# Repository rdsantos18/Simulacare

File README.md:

# SimulaCare
<<<<<<< HEAD
SimulaCare RCP
Versao WIFI + BLUETOOTH
=======
SimulaCare RCP Versao WI-FI

>>>>>>> 4a381d82d7e9b7c94d12f0bdcbb5406eb2f44847

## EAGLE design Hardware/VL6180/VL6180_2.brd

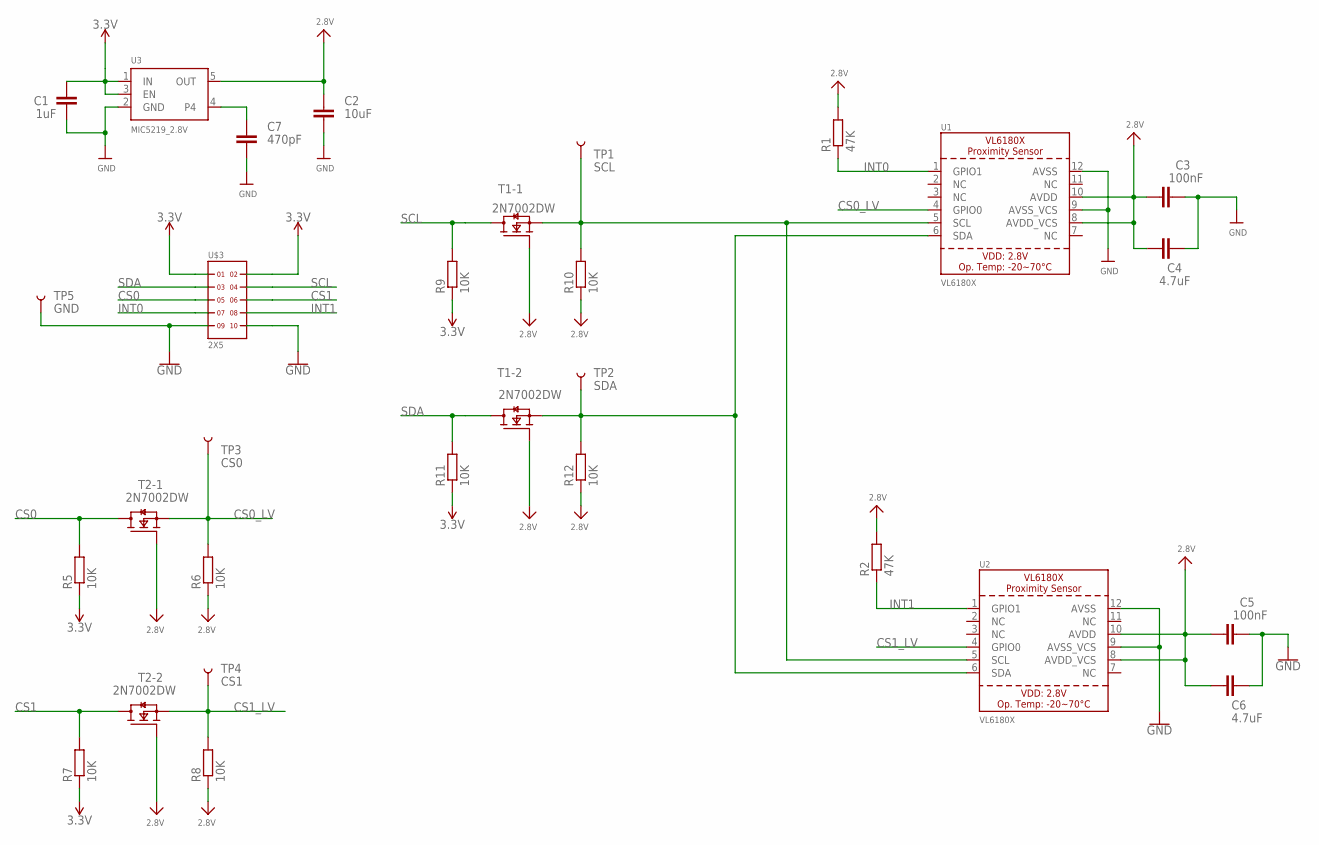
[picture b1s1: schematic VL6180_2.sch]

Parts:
C1: 1uF; C0603
C2: 10uF; C0603
C3, C5: 100nF; C0603
C4, C6: 4.7uF; C0603
C7: 470pF; C0603
R1, R2: 47K; R0603
R5, R6, R7, R8, R9, R10, R11, R12: 10K; R0603
T1, T2: 2N7002DW; SOT363
TP1: SCL; PAD.03X.04
TP2: SDA; PAD.03X.04
TP3: CS0; PAD.03X.04
TP4: CS1; PAD.03X.04
TP5: GND; PAD.03X.04
U1, U2: VL6180X; VL6180
U3: MIC5219_2.8V; SOT23-5
U$3: 2X5

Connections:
2.8V: C2.1, C3.1, C4.1, C5.1, C6.1, R1.2, R2.2, R6.1, R8.1, R10.1, R12.1, T1.2 (G), T1.5 (G), T2.2 (G), T2.5 (G), U1.8 (AVDD_VCS), U1.10 (AVDD), U2.8 (AVDD_VCS), U2.10 (AVDD), U3.5 (OUT)
3.3V: C1.1, R5.1, R7.1, R9.1, R11.1, U3.1 (IN), U3.3 (EN), U$3.1, U$3.2
CS0: R5.2, T2.6 (D), U$3.5
CS0_LV: R6.2, T2.1 (S), TP3.P$1, U1.4 (GPIO0)
CS1: R7.2, T2.3 (D), U$3.6
CS1_LV: R8.2, T2.4 (S), TP4.P$1, U2.4 (GPIO0)
GND: C1.2, C2.2, C3.2, C4.2, C5.2, C6.2, C7.2, TP5.P$1, U1.9 (AVSS_VCS), U1.12 (AVSS), U2.9 (AVSS_VCS), U2.12 (AVSS), U3.2 (GND), U$3.9, U$3.10
INT0: R1.1, U1.1 (GPIO1), U$3.7
INT1: R2.1, U2.1 (GPIO1), U$3.8
unnamed: C7.1, U3.4
unnamed: R10.2, T1.1 (S), TP1.P$1, U1.5 (SCL), U2.5 (SCL)
unnamed: R12.2, T1.4 (S), TP2.P$1, U1.6 (SDA), U2.6 (SDA)
SCL: R9.2, T1.6 (D), U$3.4
SDA: R11.2, T1.3 (D), U$3.3

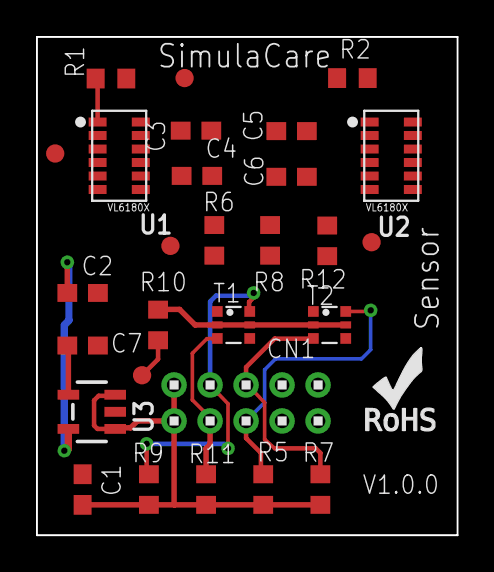
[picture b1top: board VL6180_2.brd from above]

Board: 2 copper layers, 23.4 x 27.7 mm, 29 parts (0 on the bottom side), 14 nets.

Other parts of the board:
U$20: ROHS_LOGO_0.18_IN

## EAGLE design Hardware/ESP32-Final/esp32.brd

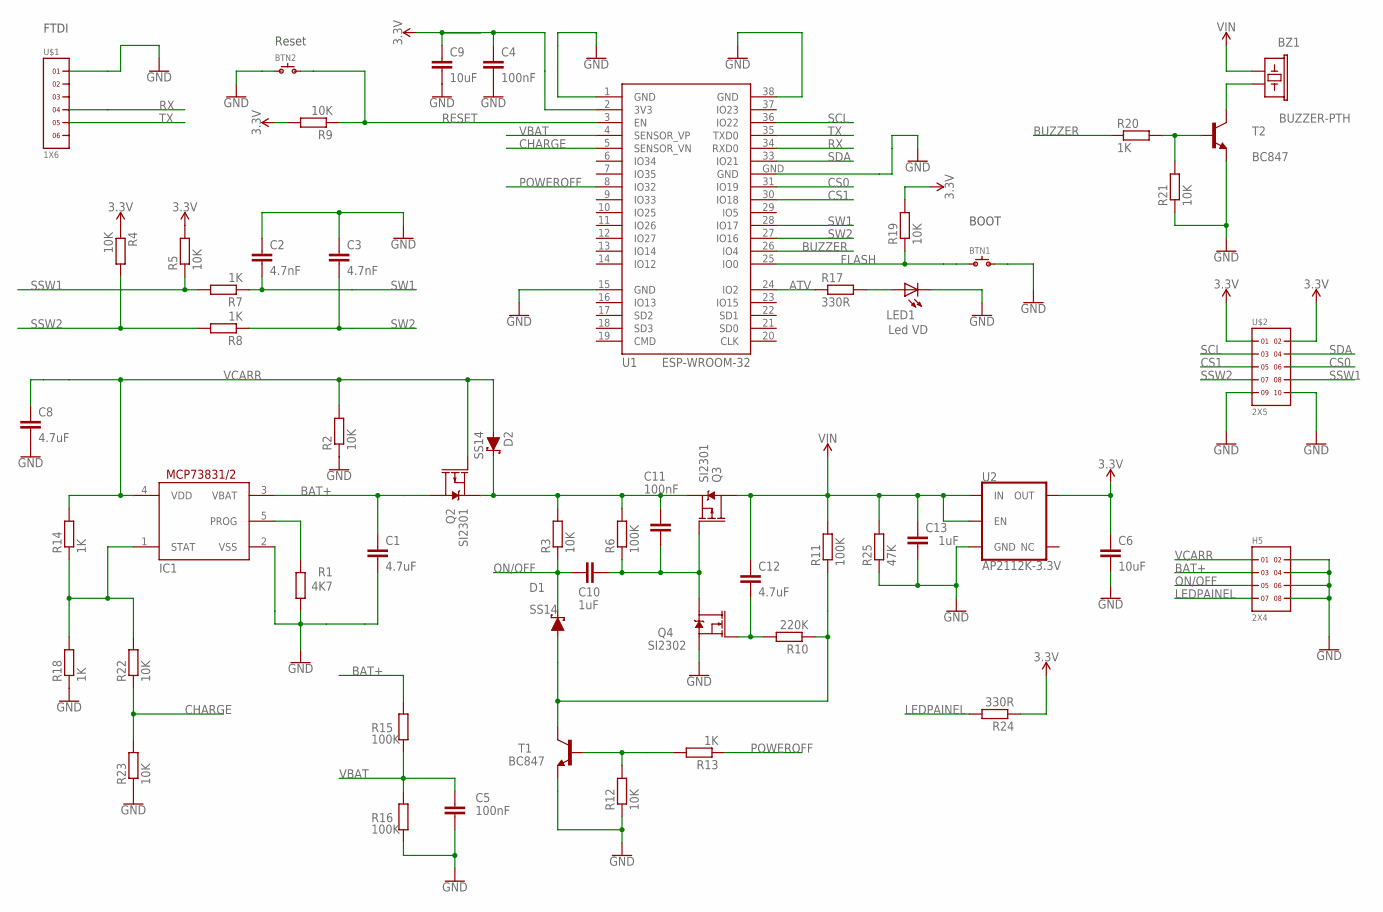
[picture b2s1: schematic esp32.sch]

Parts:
BTN1, BTN2: SPST.B3U-1000P(M); B3U-1000P(M)
BZ1: BUZZER-PTH; BUZZER-12MM
C1, C8, C12: 4.7uF; C0603
C2, C3: 4.7nF; C0603
C4, C5, C11: 100nF; C0603
C6, C9: 10uF; C0603
C10, C13: 1uF; C0603
D1, D2: SS14; SMA-DIODE
H5: 2X4
IC1: MCP73831/OT; SOT23-5L
LED1: Led VD; CHIP-LED0603
Q2, Q3: SI2301; SOT23-3
Q4: SI2302; SOT23-3
R1: 4K7; R0603
R2, R3, R4, R5, R9, R12, R19, R21, R22, R23: 10K; R0603
R6, R11, R15, R16: 100K; R0603
R7, R8, R13, R14, R18, R20: 1K; R0603
R10: 220K; R0603
R17, R24: 330R; R0603
R25: 47K; R0603
T1, T2: BC847; SOT23
U1: ESP-WROOM-32
U2: AP2112K-3.3V; SOT23-5
U$1: 1X6
U$2: 2X5

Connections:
3.3V: C4.1, C6.1, C9.1, R4.1, R5.2, R9.2, R19.2, R24.1, U1.2 (3V3), U2.5 (OUT), U$2.1, U$2.2
ATV: R17.1, U1.24 (IO2)
BAT+: C1.1, H5.3, IC1.3 (VBAT), Q2.3 (D), R15.2
BUZZER: R20.1, U1.26 (IO4)
CHARGE: R22.1, R23.2, U1.5 (SENSOR_VN)
CS0: U1.31 (IO19), U$2.6
CS1: U1.30 (IO18), U$2.5
FLASH: BTN1.1, R19.1, U1.25 (IO0)
GND: BTN1.2, BTN2.1, C1.2, C2.1, C3.1, C4.2, C5.2, C6.2, C8.2, C9.2, C13.2, H5.2, H5.4, H5.6, H5.8, IC1.2 (VSS), LED1.C, Q4.2 (S), R1.1, R2.1, R12.1, R16.1, R18.1, R21.1, R23.1, R25.1, T1.2 (E), T2.2 (E), U1.1 (GND), U1.15 (GND), U1.38 (GND), U1.GND, U2.2 (GND), U$1.1, U$2.9, U$2.10
LEDPAINEL: H5.7, R24.2
unnamed: C12.2, Q4.1 (G), R10.2
unnamed: R20.2, R21.2, T2.1 (B)
unnamed: BZ1.- (2), T2.3 (C)
unnamed: IC1.1 (STAT), R14.1, R18.2, R22.2
unnamed: C10.2, C11.1, Q3.1 (G), Q4.3 (D), R6.1
unnamed: R12.2, R13.2, T1.1 (B)
unnamed: IC1.5 (PROG), R1.2
unnamed: C11.2, D2.C, Q2.2 (S), Q3.2 (S), R3.2, R6.2
unnamed: D1.A, R10.1, R11.1, T1.3 (C)
unnamed: LED1.A, R17.2
ON/OFF: C10.1, D1.C, H5.5, R3.1
POWEROFF: R13.1, U1.8 (IO32)
RESET: BTN2.2, R9.1, U1.3 (EN)
RX: U1.34 (RXD0), U$1.4
SCL: U1.36 (IO22), U$2.3
SDA: U1.33 (IO21), U$2.4
SSW1: R5.1, R7.2, U$2.8
SSW2: R4.2, R8.2, U$2.7
SW1: C2.2, R7.1, U1.28 (IO17)
SW2: C3.2, R8.1, U1.27 (IO16)
TX: U1.35 (TXD0), U$1.5
VBAT: C5.1, R15.1, R16.2, U1.4 (SENSOR_VP)
VCARR: C8.1, D2.A, H5.1, IC1.4 (VDD), Q2.1 (G), R2.2, R14.2
VIN: BZ1.+ (1), C12.1, C13.1, Q3.3 (D), R11.2, R25.2, U2.1 (IN), U2.3 (EN)

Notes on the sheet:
Reset
BOOT
FTDI

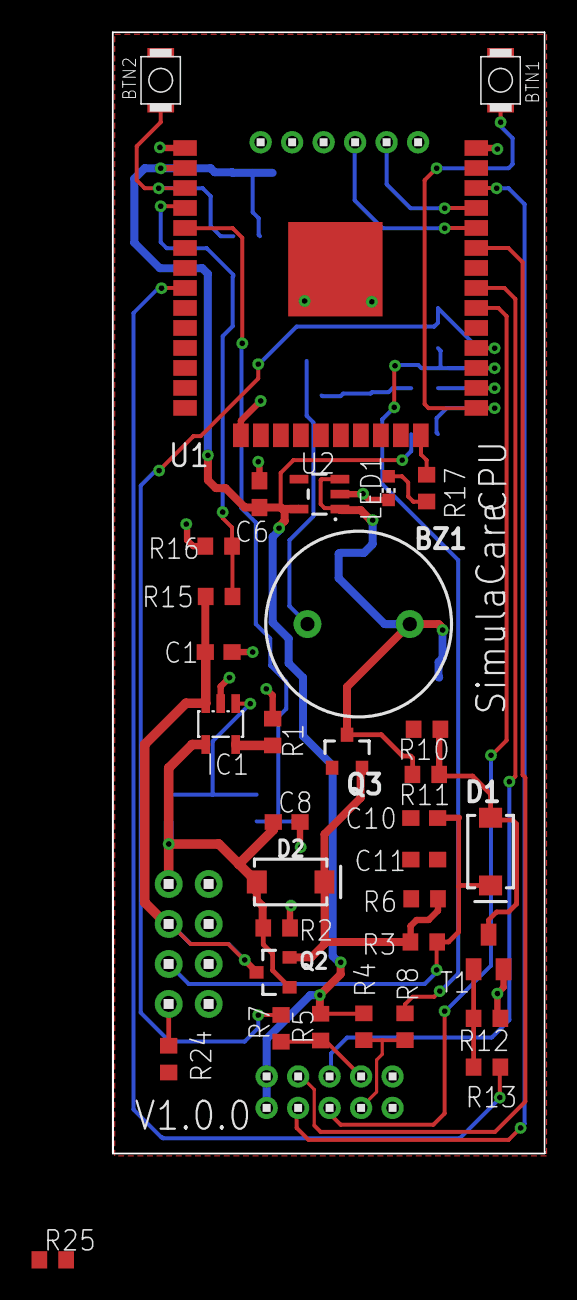
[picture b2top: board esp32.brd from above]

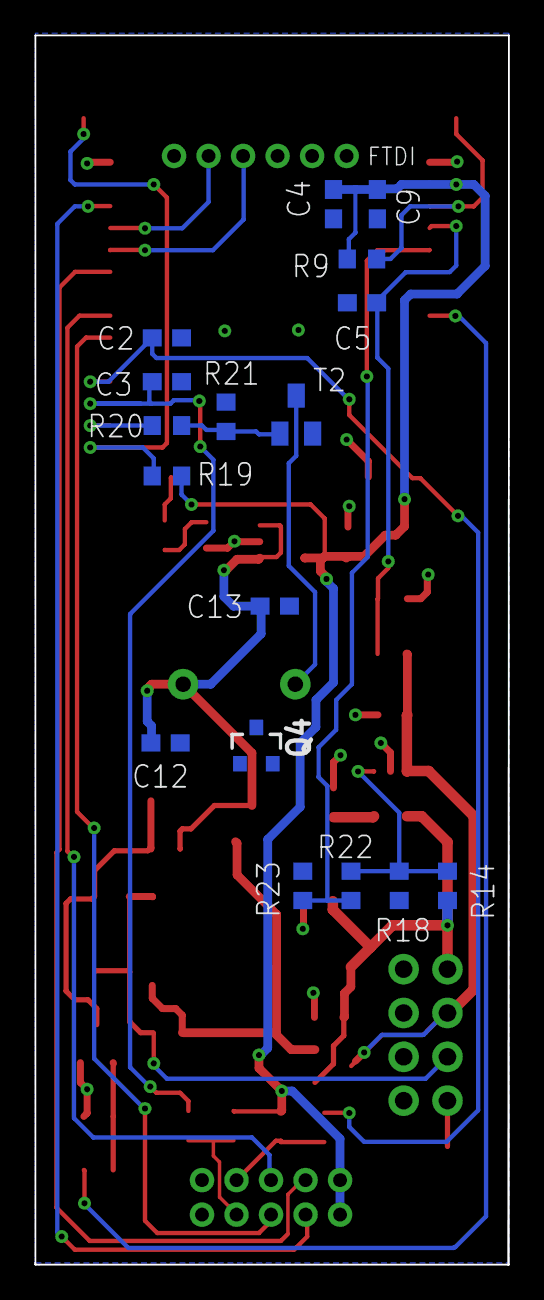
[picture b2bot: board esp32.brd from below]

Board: 2 copper layers, 27.4 x 71.2 mm, 54 parts (17 on the bottom side), 34 nets.

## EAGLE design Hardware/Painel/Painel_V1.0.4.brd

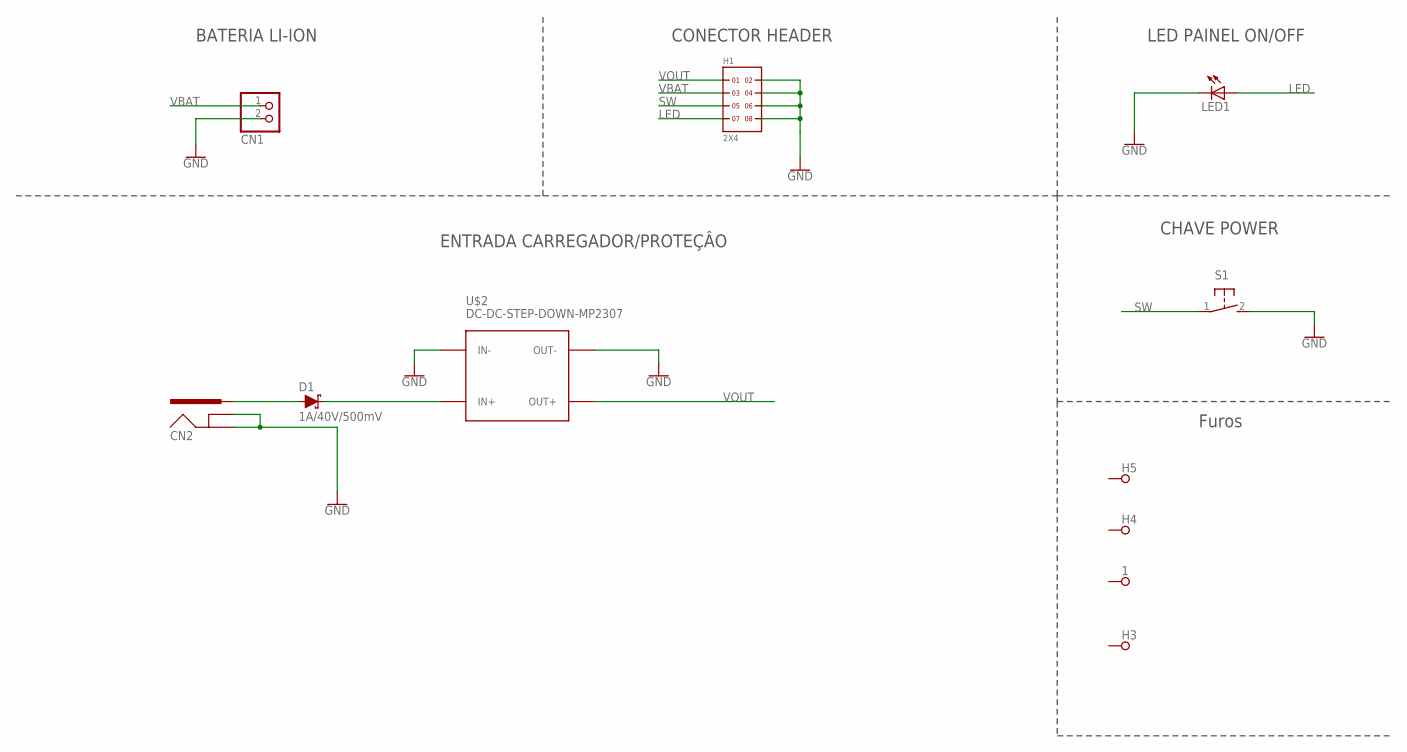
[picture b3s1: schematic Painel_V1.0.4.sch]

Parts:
1: SPECIAL_DRILL_0.1250; PAD_0.1250
CN1: JST_2PIN-THM; JST-PH-2-THM
CN2: POWERJACK
D1: 1A/40V/500mV; SMA-DIODE
H1: 2X4
H3, H4, H5: SPECIAL_DRILL_0.1250; PAD_0.1250
LED1: LED3MM
S1: 31-XX; B3F-31XX
U$2: DC-DC-STEP-DOWN-MP2307

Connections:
GND: CN1.2 (1), CN2.GND, CN2.GNDBREAK, H1.2, H1.4, H1.6, H1.8, LED1.K (C), S1.2 (S), U$2.IN-, U$2.OUT-
LED: H1.7, LED1.A
unnamed: CN2.PWR, D1.A
unnamed: D1.C, U$2.IN+
SW: H1.5, S1.1
VBAT: CN1.1 (2), H1.3
VOUT: H1.1, U$2.OUT+

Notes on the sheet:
BATERIA LI-ION
CONECTOR HEADER
LED PAINEL ON/OFF
CHAVE POWER
Furos
ENTRADA CARREGADOR/PROTEÇÂO

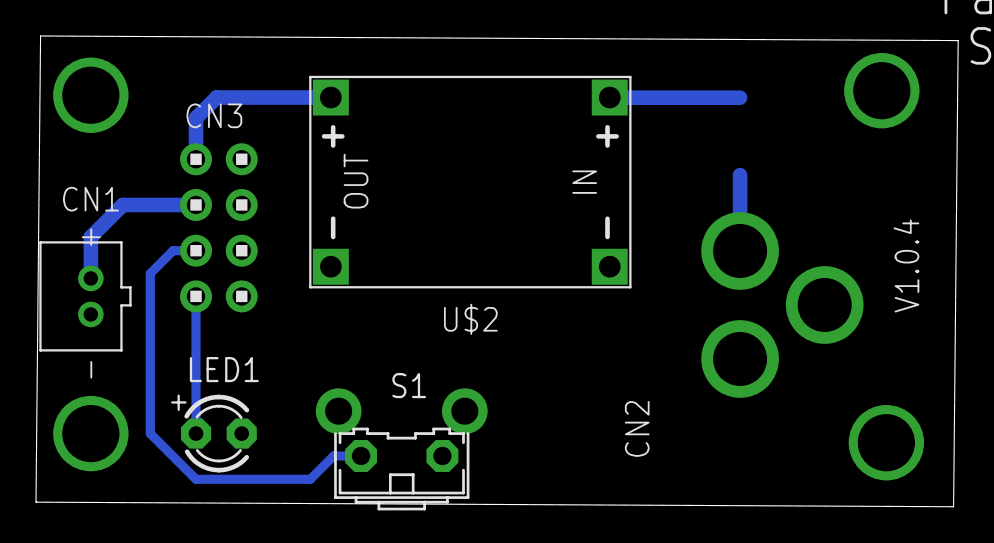
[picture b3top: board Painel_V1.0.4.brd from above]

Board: 2 copper layers, 51.2 x 26.2 mm, 12 parts (1 on the bottom side), 7 nets.

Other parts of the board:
U$1: ROHS_LOGO_0.18_IN

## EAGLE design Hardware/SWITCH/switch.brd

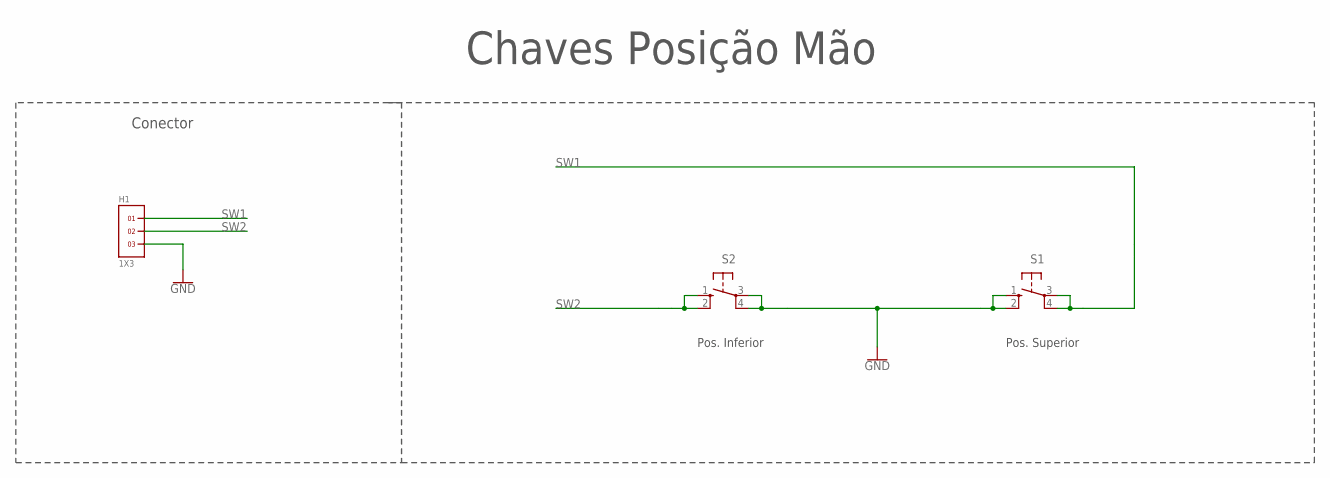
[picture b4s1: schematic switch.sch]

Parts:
H1: 1X3
S1, S2: 40-XX; B3F-40XX

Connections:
GND: H1.3, S1.1 (S), S1.2 (S1), S2.3, S2.4 (P1)
SW1: H1.1, S1.3, S1.4 (P1)
SW2: H1.2, S2.1 (S), S2.2 (S1)

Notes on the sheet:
Chaves Posição Mão
Conector
Pos. Inferior
Pos. Superior

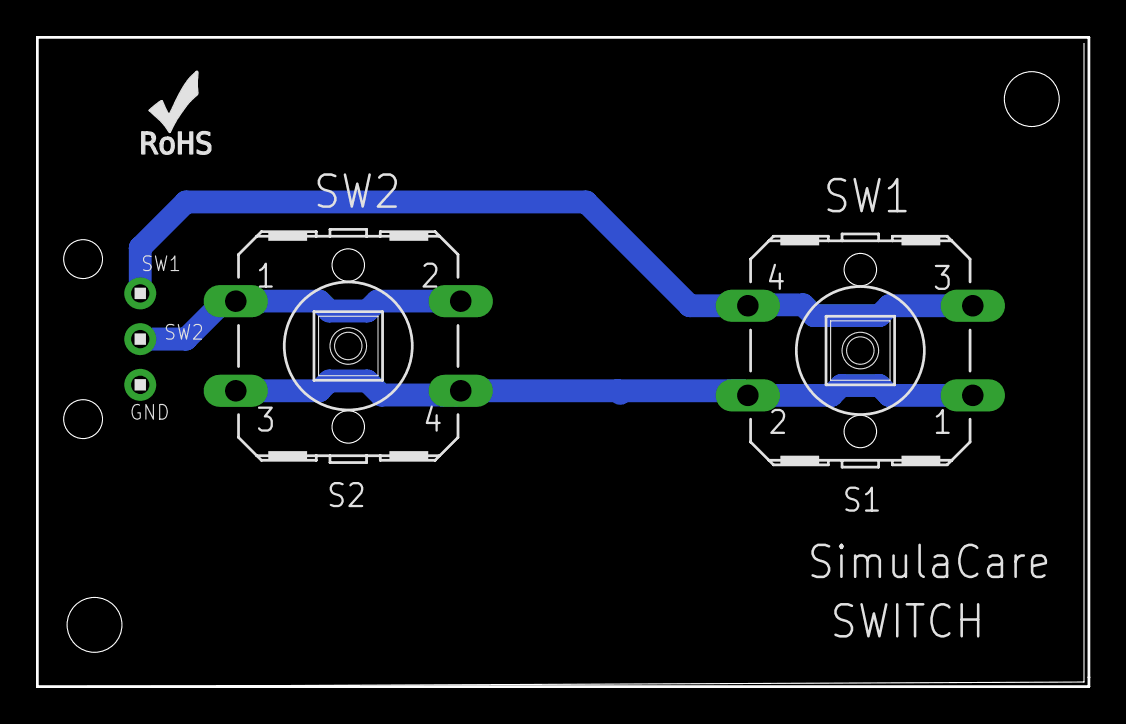
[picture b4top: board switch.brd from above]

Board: 2 copper layers, 58.4 x 36.1 mm, 4 parts (0 on the bottom side), 3 nets.

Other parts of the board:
U$1: ROHS_LOGO_0.18_IN

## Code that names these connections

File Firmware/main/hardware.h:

#include "driver/gpio.h"

// Endereços de Hardware
#define BUZZER		GPIO_NUM_4		// BUZZER
#define	POWEROFF	GPIO_NUM_32		// POWEROFF
#define	LED_ATV		GPIO_NUM_2		// LED ATV
#define	CS0			GPIO_NUM_19		// CS0
#define	CS1			GPIO_NUM_18		// CS1
#define	LED_PAINEL	GPIO_NUM_33		// Led Painel
#define	SW2			GPIO_NUM_16		// SW2
#define	SW1			GPIO_NUM_17		// SW1
#define	SW3			GPIO_NUM_35		// SW3

#define VBAT		ADC1_CHANNEL_0	// Tensao Bateria
#define CHARGE		ADC1_CHANNEL_3	// Status Carga Bateria

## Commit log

2017-08-23 Add files via upload
    Add Timer 30ms, Cadencia Led e controle do Buzzer
2017-08-24 Buzzer -> GPIO04
2017-08-29 update 29-08-17
2017-08-31 upload 31/08/17
2017-09-14 Update 14/09/2017
    Update 14/09/2017
2017-09-19 Update 19-09-2017
    Update 19-09-2017
2017-10-03 update 02-10-2017
2017-10-16 Version 1.0.0
    PCB v1.0.0
2017-10-16 V1.0.2
    PCB v1.0.2
2017-10-16 V1.0.1
    PCB v1.0.1
2017-10-16 v1.0.0
    PCB v1.0.0
2017-11-20 Create teste
2017-11-27 Create esp-idf
2017-12-15 Initial Commit
    Version esp-idf
2017-12-15 Add Mongoose Files
2017-12-15 Add component.mk
2017-12-15 gitignore
2017-12-15 add gitignore
2017-12-15 teste
2018-01-09 Update BLE
2018-01-17 Versao WI-FI Polling 10ms, Send Frame 500ms, 5 bytes a 100ms:
2018-01-17 Bluetooth Added
2018-01-19 Up Date
2018-01-26 update mDNS
2018-01-26 Add Tools Plot Values

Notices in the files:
parts and their libraries:
SparkFun-Electromechanical: Licensing: Creative Commons ShareAlike 4.0 International - https://creativecommons.org/licenses/by-sa/4.0
esp32: Creative Commons Attribution-ShareAlike 4.0 International
